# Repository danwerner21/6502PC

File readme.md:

# 6809PC
The 6502PC is a 6502 ATX format board with 512K RAM, 4K ROM, with a flexible programmable MMU, battery backed up RTC, 6551 UART, and 6 ISAish slots.  This computer will run a version of DOS/65 by Richard A. Leary.  

See this repo (https://github.com/danwerner21/6x0x-DOS65) for ROM image and operating system.

## BUGS
On the V1.0 board /VMA is not asserted long enough and needs to be just tied to ground.

Patches:
 Lift Pin 1 of u5 74ls02.  Tie the socket of U5 pin 1 to ground.
 U47 SCRATCH CONNECTION TO PIN 3 ON BOTTOM OF PCB.  TIE U47 PIN 3 TO +5V (DO NOT USE PIN 18 OF U47)

Contrary to what is on the Schematic, the battery connector will not support a supercap, a battery is required.

This is corrected on the V1.1 board.

### Jumper Settings
        J1 - IRQ ASSIGNMENT FOR SLOT J2
        J2 - IRQ ASSIGNMENT FOR SLOT J4
        J5 - IRQ ASSIGNMENT FOR SLOT J6
        J7 - IRQ ASSIGNMENT FOR SLOT J8
        J9 - IRQ ASSIGNMENT FOR SLOT J10        
        J13 - IRQ ASSIGNMENT FOR SLOT J14
        
        K1 - ROM BANK SELECT 1&2-ROM IMAGE AT $6000-$6FFF  3&4-ROM IMAGE AT $7000-$7FFF
        P12- POWER SWITCH (MOMENTARY, ATX CASE SWITCH)
        JP1- RESET SWITCH (MOMENTARY, ATX CASE SWITCH)
        P16- BATTERY CONNECTION, P1=+ P2-4=-  (NON RECHARGEABLE)
        JP3- CTS FORCE HIGH
        P18- CONSOLE SERIAL CONNECTOR
        J11- TTL CONSOLE SERIAL CONNECTOR
        J12- ENABLE POWER TO TTL CONSOLE SERIAL CONNECTOR

### Building the system

### Default Memory Map
            $0000-$E000 - RAM
            $E000-$EFFF - Memory Mapped IO
            $F000-$FFFF - ROM
#### IO MEMORY MAP
            $E000-$EF7F - ISA IO SPACE
            $EF80-$EF8F - ACIA
            $EF90-$EF9F - RTC
            $EFA0-$EFAF - OPEN
            $EFB0-$EFBF - OPEN
            $EFC0-$EFCF - OPEN
            $EFD0-$EFDF - MMU TASK MAP
            $EFE0-$EFEF - MMU REGISTERS
            $EFF0-$EFFF - OPEN

### Bill Of Materials
Reference|Value|Qty|Field1|Description
---------|-----|---|------|-----------
C1-C4,C17|22 uF|5||Polarized capacitor
C5-C16,C18-C27,C29-C33,C36-C54,C56,C58,C62|0.1 uF|49||Unpolarized capacitor
C28|1uF|1||Polarized capacitor
C35|10uF|1||Polarized capacitor
C57|0.01 uF|1||Unpolarized capacitor
C59,C60|15pf|2||Unpolarized capacitor
C61,C63-C66|1.0 uF|5||Polarized capacitor
D1,D2|1N4148|2||Diode
D3,D4|D|2||Diode
J1,J2,J5,J7,J9,J13|IRQ Selection|6||Generic connector, double row, 02x06, odd/even pin numbering scheme (row 1 odd numbers, row 2 even numbers), script generated (kicad-library-utils/schlib/autogen/connector/)
J3,J4,J6,J8,J10,J14|Bus_ISA_8bit|6||8-bit ISA-PC bus connector
J11|TTL SERIAL CONSOLE|1||Generic connector, single row, 01x06, script generated (kicad-library-utils/schlib/autogen/connector/)
J12|TTL CONSOLE PWR|1||Generic connector, single row, 01x02, script generated (kicad-library-utils/schlib/autogen/connector/)
JP1,JP3|JUMPER|2||Generic connector, single row, 01x02, script generated (kicad-library-utils/schlib/autogen/connector/),Jumper, 2-pole, open
K1|ROM SELECT|1||Generic connector, single row, 01x03, script generated (kicad-library-utils/schlib/autogen/connector/)
P1|SHADOW ADDR|1||Generic connector, double row, 02x04, odd/even pin numbering scheme (row 1 odd numbers, row 2 even numbers), script generated (kicad-library-utils/schlib/autogen/connector/)
P11|CONN_10X2|1||Generic connector, double row, 02x10, odd/even pin numbering scheme (row 1 odd numbers, row 2 even numbers), script generated (kicad-library-utils/schlib/autogen/connector/)
P12|POWER_SW|1||Generic connector, single row, 01x02, script generated (kicad-library-utils/schlib/autogen/connector/)
P13|14.31818 MHz CLK|1||
P14|16.000Mhz|1||
P15|CPU CLOCK SPEED|1||Generic connector, double row, 02x04, odd/even pin numbering scheme (row 1 odd numbers, row 2 even numbers), script generated (kicad-library-utils/schlib/autogen/connector/)
P16|CONN_4|1||Generic connector, single row, 01x04, script generated (kicad-library-utils/schlib/autogen/connector/)
P17|1.8432 MHz CLK|1||
P18|SERIAL|1||Generic connector, double row, 02x05, odd/even pin numbering scheme (row 1 odd numbers, row 2 even numbers), script generated (kicad-library-utils/schlib/autogen/connector/)
R1,R3|10k|2||Resistor
R2|470|1||Resistor
R4,R7,R26|4.7K|3||Resistor
R5,R6,R8|1000|3||Resistor
RR1|2200|1||9 resistor network, star topology, bussed resistors, small symbol
RR2|22K|1||9 resistor network, star topology, bussed resistors, small symbol
SW1|POWER|1||Push button switch, generic, two pins
SW2|RESET|1||Push button switch, generic, two pins
U1|74LS04|1||Hex Inverter
U2,U34,U36,U39,U45,U46|74LS244|6||Octal Buffer and Line Driver With 3-State Output, active-low enables, non-inverting outputs
U3|74LS682|1||
U4|74LS86|1||Quad 2-input XOR
U5|74LS02|1||quad 2-input NOR gate
U6,U21|74LS00|2||quad 2-input NAND gate
U7,U10,U16|74LS32|3||Quad 2-input OR
U8|SRAM_512K|1||512K x 8 Low Power CMOS RAM, DIP-32
U9,U15|74LS08|2||Quad And2
U11|27C256|1||OTP EPROM 256 KiBit
U12,U22|74LS74|2||Dual D Flip-flop, Set & Reset
U13|6502|1||8-bit NMOS Microprocessor, 64K, DIP-40
U17|74LS14|1||Hex inverter schmitt trigger
U18|74LS06|1||Inverter Open Collect
U19|74HCT14|1||Hex inverter schmitt trigger
U23|74LS688|1||8-bit magnitude comparator
U24,U42|74LS138|2||Decoder 3 to 8 active low outputs
U25-U28,U32,U41|74LS245|6||Octal BUS Transceivers, 3-State outputs
U29|DS1233|1||
U30|74LS163|1||Synchronous 4-bit programmable binary Counter
U31|74LS240|1||Octal Buffer and Line Driver With 3-State Output, active-low enables, inverting outputs
U35|74LS174|1||Hex D-type Flip-Flop, reset
U37|74LS157|1||Quad 2 to 1 line Multiplexer
U38|74LS374|1||8-bit Register, 3-state outputs
U40|SRAM-32K|1||256K (32K x 8) Static RAM, 70ns, DIP-28
U43,U44|74LS257|2||Quad 2 to 1 Multiplexer
U47|M6242|1||M6242
U48|G65SC51P|1||CMOS Asynchronous Communication Interface Adapter (ACIA), Serial UART, DIP-28
U49|MAX232|1||Dual RS232 driver/receiver, 5V supply, 120kb/s, 0C-70C
X1|RTC_OSC|1|32.768 KHz|Two pin crystal

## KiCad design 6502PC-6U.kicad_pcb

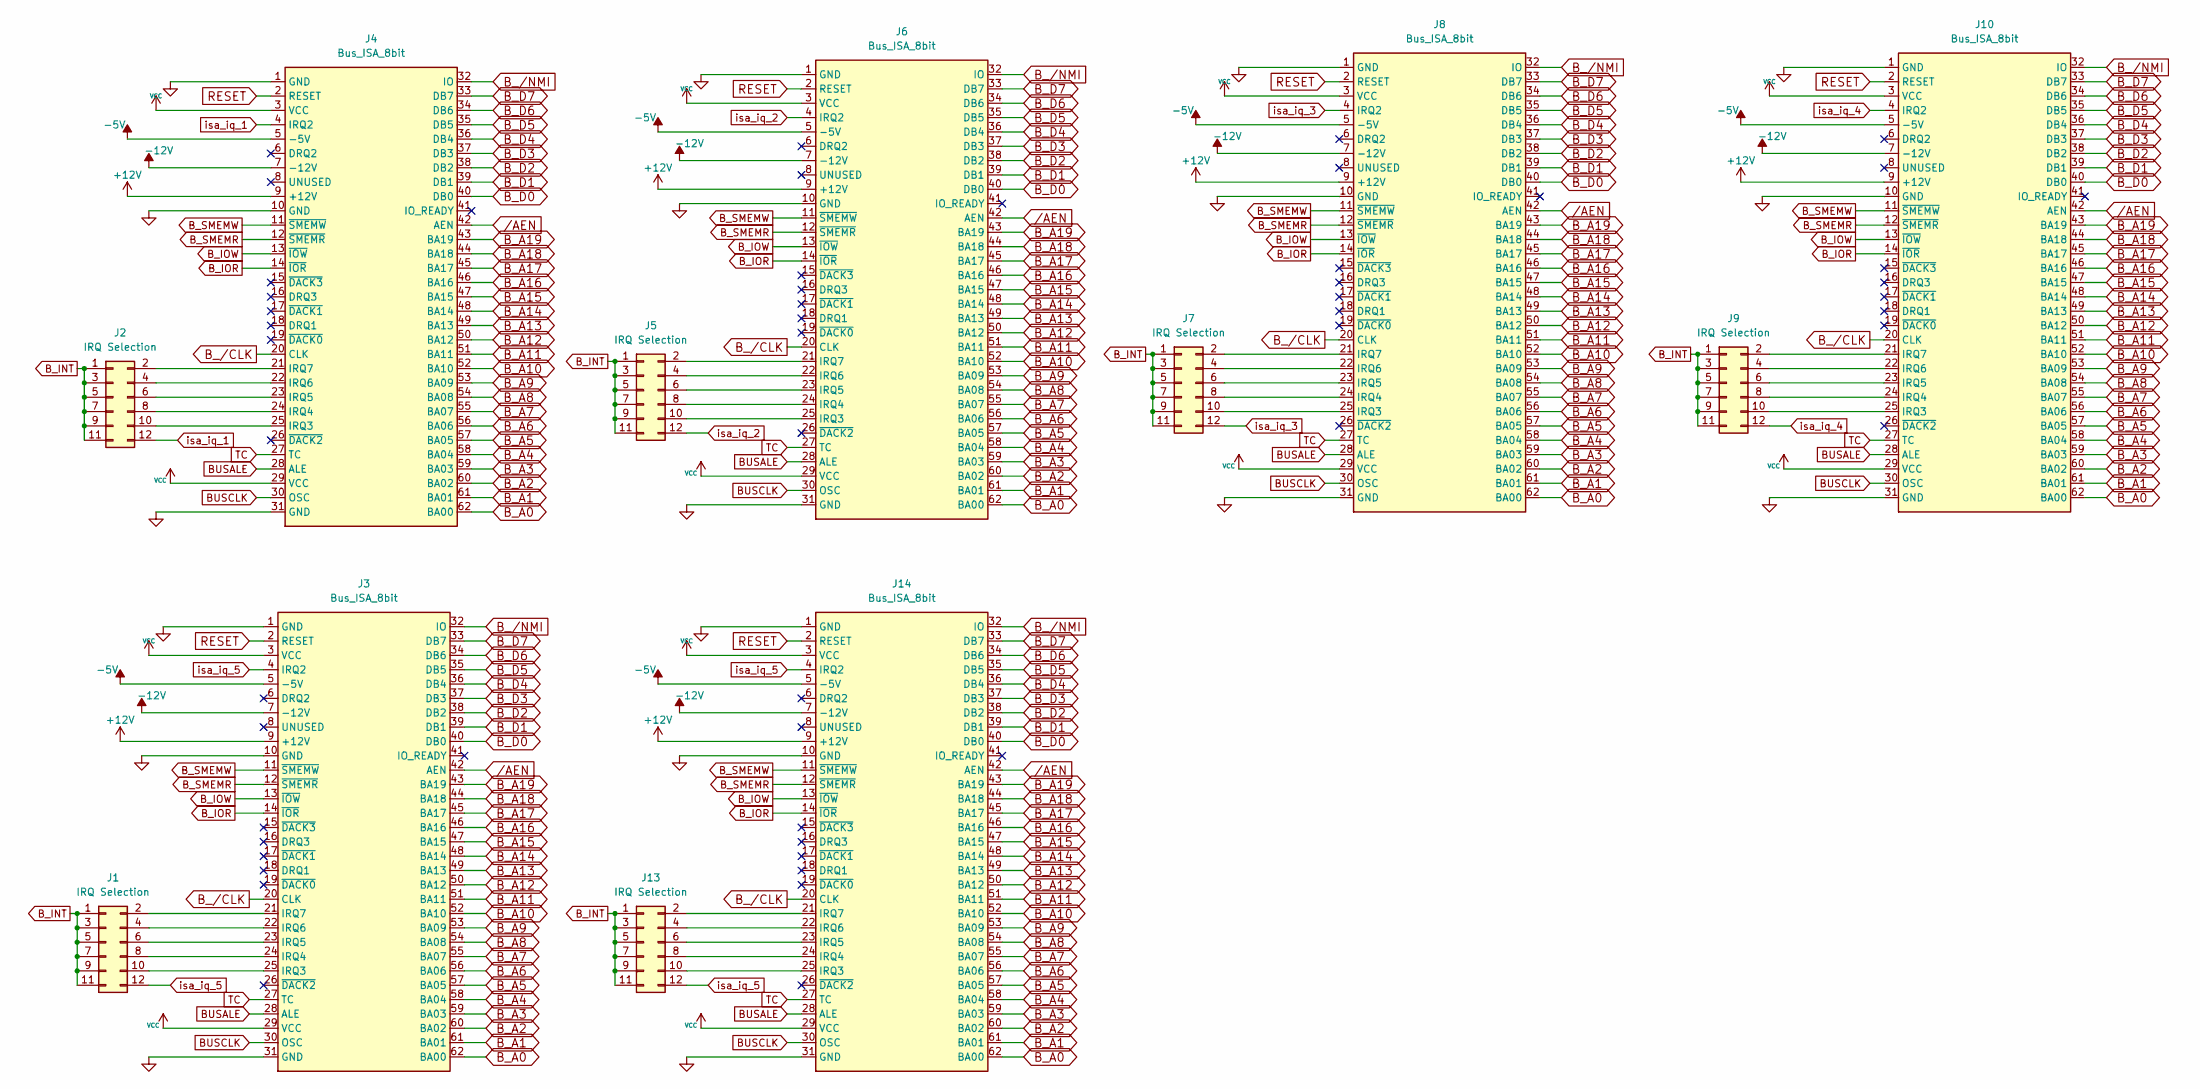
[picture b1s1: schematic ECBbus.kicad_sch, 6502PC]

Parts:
J1, J2, J5, J7, J9, J13: IRQ Selection; STD_DDW_PINHEAD_V_2x06
J3, J4, J6, J8, J10, J14: Bus_ISA_8bit; BUSPC_HOST

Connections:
+5V: J3.3 (VCC), J3.29 (VCC), J4.3 (VCC), J4.29 (VCC), J6.3 (VCC), J6.29 (VCC), J8.3 (VCC), J8.29 (VCC), J10.3 (VCC), J10.29 (VCC), J14.3 (VCC), J14.29 (VCC); also elsewhere on the board
+12V: J3.9 (+12V), J4.9 (+12V), J6.9 (+12V), J8.9 (+12V), J10.9 (+12V), J14.9 (+12V); also elsewhere on the board
-5V: J3.5 (-5V), J4.5 (-5V), J6.5 (-5V), J8.5 (-5V), J10.5 (-5V), J14.5 (-5V); also elsewhere on the board
-12V: J3.7 (-12V), J4.7 (-12V), J6.7 (-12V), J8.7 (-12V), J10.7 (-12V), J14.7 (-12V); also elsewhere on the board
BUSALE: J3.28 (ALE), J4.28 (ALE), J6.28 (ALE), J8.28 (ALE), J10.28 (ALE), J14.28 (ALE); also elsewhere on the board
BUSCLK: J3.30 (OSC), J4.30 (OSC), J6.30 (OSC), J8.30 (OSC), J10.30 (OSC), J14.30 (OSC); also elsewhere on the board
B_A0: J3.62 (BA00), J4.62 (BA00), J6.62 (BA00), J8.62 (BA00), J10.62 (BA00), J14.62 (BA00); also elsewhere on the board
B_A1: J3.61 (BA01), J4.61 (BA01), J6.61 (BA01), J8.61 (BA01), J10.61 (BA01), J14.61 (BA01); also elsewhere on the board
B_A2: J3.60 (BA02), J4.60 (BA02), J6.60 (BA02), J8.60 (BA02), J10.60 (BA02), J14.60 (BA02); also elsewhere on the board
B_A3: J3.59 (BA03), J4.59 (BA03), J6.59 (BA03), J8.59 (BA03), J10.59 (BA03), J14.59 (BA03); also elsewhere on the board
B_A4: J3.58 (BA04), J4.58 (BA04), J6.58 (BA04), J8.58 (BA04), J10.58 (BA04), J14.58 (BA04); also elsewhere on the board
B_A5: J3.57 (BA05), J4.57 (BA05), J6.57 (BA05), J8.57 (BA05), J10.57 (BA05), J14.57 (BA05); also elsewhere on the board
B_A6: J3.56 (BA06), J4.56 (BA06), J6.56 (BA06), J8.56 (BA06), J10.56 (BA06), J14.56 (BA06); also elsewhere on the board
B_A7: J3.55 (BA07), J4.55 (BA07), J6.55 (BA07), J8.55 (BA07), J10.55 (BA07), J14.55 (BA07); also elsewhere on the board
B_A8: J3.54 (BA08), J4.54 (BA08), J6.54 (BA08), J8.54 (BA08), J10.54 (BA08), J14.54 (BA08); also elsewhere on the board
B_A9: J3.53 (BA09), J4.53 (BA09), J6.53 (BA09), J8.53 (BA09), J10.53 (BA09), J14.53 (BA09); also elsewhere on the board
B_A10: J3.52 (BA10), J4.52 (BA10), J6.52 (BA10), J8.52 (BA10), J10.52 (BA10), J14.52 (BA10); also elsewhere on the board
B_A11: J3.51 (BA11), J4.51 (BA11), J6.51 (BA11), J8.51 (BA11), J10.51 (BA11), J14.51 (BA11); also elsewhere on the board
B_A12: J3.50 (BA12), J4.50 (BA12), J6.50 (BA12), J8.50 (BA12), J10.50 (BA12), J14.50 (BA12); also elsewhere on the board
B_A13: J3.49 (BA13), J4.49 (BA13), J6.49 (BA13), J8.49 (BA13), J10.49 (BA13), J14.49 (BA13); also elsewhere on the board
B_A14: J3.48 (BA14), J4.48 (BA14), J6.48 (BA14), J8.48 (BA14), J10.48 (BA14), J14.48 (BA14); also elsewhere on the board
B_A15: J3.47 (BA15), J4.47 (BA15), J6.47 (BA15), J8.47 (BA15), J10.47 (BA15), J14.47 (BA15); also elsewhere on the board
B_A16: J3.46 (BA16), J4.46 (BA16), J6.46 (BA16), J8.46 (BA16), J10.46 (BA16), J14.46 (BA16); also elsewhere on the board
B_A17: J3.45 (BA17), J4.45 (BA17), J6.45 (BA17), J8.45 (BA17), J10.45 (BA17), J14.45 (BA17); also elsewhere on the board
B_A18: J3.44 (BA18), J4.44 (BA18), J6.44 (BA18), J8.44 (BA18), J10.44 (BA18), J14.44 (BA18); also elsewhere on the board
B_A19: J3.43 (BA19), J4.43 (BA19), J6.43 (BA19), J8.43 (BA19), J10.43 (BA19), J14.43 (BA19); also elsewhere on the board
B_D0: J3.40 (DB0), J4.40 (DB0), J6.40 (DB0), J8.40 (DB0), J10.40 (DB0), J14.40 (DB0); also elsewhere on the board
B_D1: J3.39 (DB1), J4.39 (DB1), J6.39 (DB1), J8.39 (DB1), J10.39 (DB1), J14.39 (DB1); also elsewhere on the board
B_D2: J3.38 (DB2), J4.38 (DB2), J6.38 (DB2), J8.38 (DB2), J10.38 (DB2), J14.38 (DB2); also elsewhere on the board
B_D3: J3.37 (DB3), J4.37 (DB3), J6.37 (DB3), J8.37 (DB3), J10.37 (DB3), J14.37 (DB3); also elsewhere on the board
B_D4: J3.36 (DB4), J4.36 (DB4), J6.36 (DB4), J8.36 (DB4), J10.36 (DB4), J14.36 (DB4); also elsewhere on the board
B_D5: J3.35 (DB5), J4.35 (DB5), J6.35 (DB5), J8.35 (DB5), J10.35 (DB5), J14.35 (DB5); also elsewhere on the board
B_D6: J3.34 (DB6), J4.34 (DB6), J6.34 (DB6), J8.34 (DB6), J10.34 (DB6), J14.34 (DB6); also elsewhere on the board
B_D7: J3.33 (DB7), J4.33 (DB7), J6.33 (DB7), J8.33 (DB7), J10.33 (DB7), J14.33 (DB7); also elsewhere on the board
B_INT: J1.1, J1.3, J1.5, J1.7, J1.9, J1.11, J2.1, J2.3, J2.5, J2.7, J2.9, J2.11, J5.1, J5.3, J5.5, J5.7, J5.9, J5.11, J7.1, J7.3, J7.5, J7.7, J7.9, J7.11, J9.1, J9.3, J9.5, J9.7, J9.9, J9.11, J13.1, J13.3, J13.5, J13.7, J13.9, J13.11; also elsewhere on the board
B_IOR: J3.14 (~IOR), J4.14 (~IOR), J6.14 (~IOR), J8.14 (~IOR), J10.14 (~IOR), J14.14 (~IOR); also elsewhere on the board
B_IOW: J3.13 (~IOW), J4.13 (~IOW), J6.13 (~IOW), J8.13 (~IOW), J10.13 (~IOW), J14.13 (~IOW); also elsewhere on the board
B_SMEMR: J3.12 (~SMEMR), J4.12 (~SMEMR), J6.12 (~SMEMR), J8.12 (~SMEMR), J10.12 (~SMEMR), J14.12 (~SMEMR); also elsewhere on the board
B_SMEMW: J3.11 (~SMEMW), J4.11 (~SMEMW), J6.11 (~SMEMW), J8.11 (~SMEMW), J10.11 (~SMEMW), J14.11 (~SMEMW); also elsewhere on the board
B_/CLK: J3.20 (CLK), J4.20 (CLK), J6.20 (CLK), J8.20 (CLK), J10.20 (CLK), J14.20 (CLK); also elsewhere on the board
B_/NMI: J3.32 (IO), J4.32 (IO), J6.32 (IO), J8.32 (IO), J10.32 (IO), J14.32 (IO); also elsewhere on the board
GND: J3.1 (GND), J3.10 (GND), J3.31 (GND), J4.1 (GND), J4.10 (GND), J4.31 (GND), J6.1 (GND), J6.10 (GND), J6.31 (GND), J8.1 (GND), J8.10 (GND), J8.31 (GND), J10.1 (GND), J10.10 (GND), J10.31 (GND), J14.1 (GND), J14.10 (GND), J14.31 (GND); also elsewhere on the board
unnamed: J1.2, J3.21 (IRQ7)
unnamed: J1.4, J3.22 (IRQ6)
unnamed: J1.6, J3.23 (IRQ5)
unnamed: J1.8, J3.24 (IRQ4)
unnamed: J1.10, J3.25 (IRQ3)
unnamed: J2.2, J4.21 (IRQ7)
unnamed: J2.4, J4.22 (IRQ6)
unnamed: J2.6, J4.23 (IRQ5)
unnamed: J2.8, J4.24 (IRQ4)
unnamed: J2.10, J4.25 (IRQ3)
unnamed: J5.2, J6.21 (IRQ7)
unnamed: J5.4, J6.22 (IRQ6)
unnamed: J5.6, J6.23 (IRQ5)
unnamed: J5.8, J6.24 (IRQ4)
unnamed: J5.10, J6.25 (IRQ3)
unnamed: J7.2, J8.21 (IRQ7)
unnamed: J7.4, J8.22 (IRQ6)
unnamed: J7.6, J8.23 (IRQ5)
unnamed: J7.8, J8.24 (IRQ4)
unnamed: J7.10, J8.25 (IRQ3)
unnamed: J9.10, J10.25 (IRQ3)
unnamed: J9.8, J10.24 (IRQ4)
unnamed: J9.6, J10.23 (IRQ5)
unnamed: J9.4, J10.22 (IRQ6)
unnamed: J9.2, J10.21 (IRQ7)
unnamed: J13.2, J14.21 (IRQ7)
unnamed: J13.4, J14.22 (IRQ6)
unnamed: J13.6, J14.23 (IRQ5)
unnamed: J13.8, J14.24 (IRQ4)
unnamed: J13.10, J14.25 (IRQ3)
RESET: J3.2 (RESET), J4.2 (RESET), J6.2 (RESET), J8.2 (RESET), J10.2 (RESET), J14.2 (RESET); also elsewhere on the board
TC: J3.27 (TC), J4.27 (TC), J6.27 (TC), J8.27 (TC), J10.27 (TC), J14.27 (TC); also elsewhere on the board
isa_iq_1: J2.12, J4.4 (IRQ2)
isa_iq_2: J5.12, J6.4 (IRQ2)
isa_iq_3: J7.12, J8.4 (IRQ2)
isa_iq_4: J9.12, J10.4 (IRQ2)
isa_iq_5: J1.12, J3.4 (IRQ2), J13.12, J14.4 (IRQ2)
/AEN: J3.42 (AEN), J4.42 (AEN), J6.42 (AEN), J8.42 (AEN), J10.42 (AEN), J14.42 (AEN); also elsewhere on the board

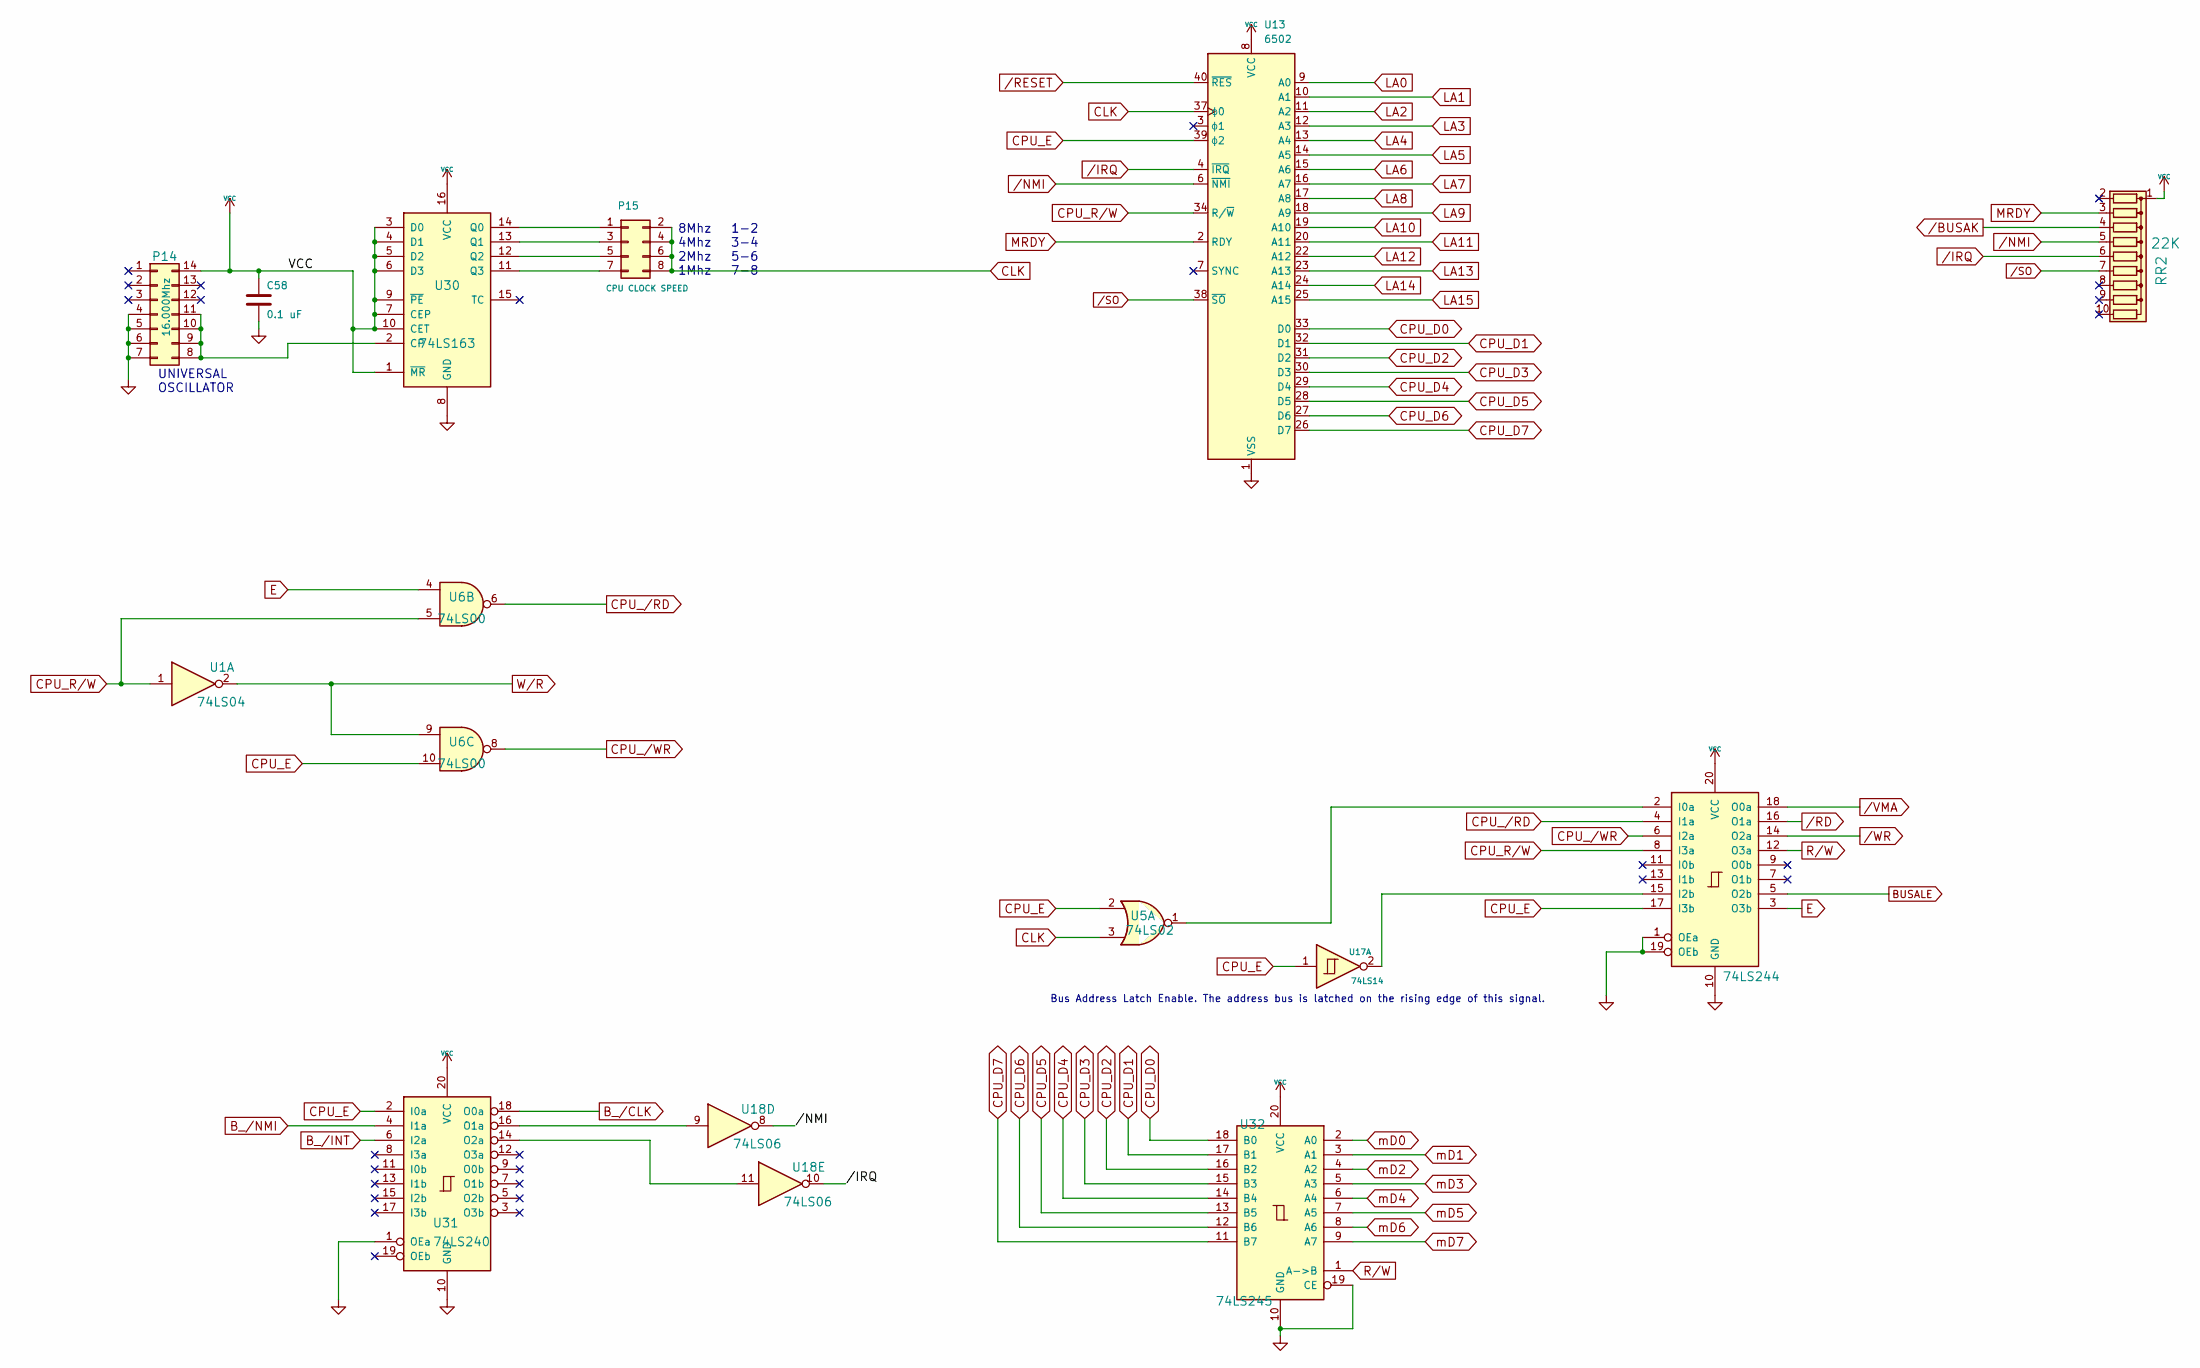
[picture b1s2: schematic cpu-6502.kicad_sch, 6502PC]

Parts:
C58: 0.1 uF; STD_DDW_CAP
P14: 16.000Mhz; STD_DDW_DIP14
P15: CPU CLOCK SPEED; STD_DDW_PINHEAD_V_2x04
RR2: 22K; STD_DDW_SIP10
U1: 74LS04; STD_DDW_DIP14
U5: 74LS02; STD_DDW_DIP14
U6: 74LS00; STD_DDW_DIP14
U13: 6502; DIP-40_W15.24mm
U17: 74LS14; STD_DDW_DIP14
U18: 74LS06; STD_DDW_DIP14
U30: 74LS163; STD_DDW_DIP16
U31: 74LS240; STD_DDW_DIP20
U32: 74LS245; STD_DDW_DIP20
U34: 74LS244; STD_DDW_DIP20

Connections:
+5V: C58.1, P14.14, RR2.1 (common), U13.8 (VCC), U30.1 (~MR), U30.3 (D0), U30.4 (D1), U30.5 (D2), U30.6 (D3), U30.7 (CEP), U30.9 (~PE), U30.10 (CET), U30.16 (VCC), U31.20 (VCC), U32.20 (VCC), U34.20 (VCC); also elsewhere on the board
BUSALE: U34.5 (O2b); also elsewhere on the board
B_/CLK: U31.18 (O0a); also elsewhere on the board
B_/INT: U31.6 (I2a); also elsewhere on the board
B_/NMI: U31.4 (I1a); also elsewhere on the board
CLK: P15.2, P15.4, P15.6, P15.8, U5.3, U13.37 (ϕ0)
CPU_D0: U13.33 (D0), U32.18 (B0)
CPU_D1: U13.32 (D1), U32.17 (B1)
CPU_D2: U13.31 (D2), U32.16 (B2)
CPU_D3: U13.30 (D3), U32.15 (B3)
CPU_D4: U13.29 (D4), U32.14 (B4)
CPU_D5: U13.28 (D5), U32.13 (B5)
CPU_D6: U13.27 (D6), U32.12 (B6)
CPU_D7: U13.26 (D7), U32.11 (B7)
CPU_E: U5.2, U6.10, U13.39 (ϕ2), U17.1, U31.2 (I0a), U34.17 (I3b); also elsewhere on the board
CPU_R/W: U1.1, U6.5, U13.34 (R/~W), U34.8 (I3a); also elsewhere on the board
CPU_/RD: U6.6, U34.4 (I1a); also elsewhere on the board
CPU_/WR: U6.8, U34.6 (I2a); also elsewhere on the board
E: U6.4, U34.3 (O3b); also elsewhere on the board
GND: C58.2, P14.4, P14.5, P14.6, P14.7, U13.1 (VSS), U13.21 (VSS), U30.8 (GND), U31.1 (OEa), U31.10 (GND), U32.10 (GND), U32.19 (CE), U34.1 (OEa), U34.10 (GND), U34.19 (OEb); also elsewhere on the board
LA0: U13.9 (A0); also elsewhere on the board
LA1: U13.10 (A1); also elsewhere on the board
LA2: U13.11 (A2); also elsewhere on the board
LA3: U13.12 (A3); also elsewhere on the board
LA4: U13.13 (A4); also elsewhere on the board
LA5: U13.14 (A5); also elsewhere on the board
LA6: U13.15 (A6); also elsewhere on the board
LA7: U13.16 (A7); also elsewhere on the board
LA8: U13.17 (A8); also elsewhere on the board
LA9: U13.18 (A9); also elsewhere on the board
LA10: U13.19 (A10); also elsewhere on the board
LA11: U13.20 (A11); also elsewhere on the board
LA12: U13.22 (A12); also elsewhere on the board
LA13: U13.23 (A13); also elsewhere on the board
LA14: U13.24 (A14); also elsewhere on the board
LA15: U13.25 (A15); also elsewhere on the board
MRDY: RR2.3 (R2), U13.2 (RDY)
unnamed: P15.1, U30.14 (Q0)
unnamed: P15.3, U30.13 (Q1)
unnamed: P15.5, U30.12 (Q2)
unnamed: P15.7, U30.11 (Q3)
unnamed: P14.8, P14.9, P14.10, P14.11, U30.2 (CP)
unnamed: U18.9, U31.16 (O1a)
unnamed: U18.11, U31.14 (O2a)
unnamed: U5.1, U34.2 (I0a)
unnamed: U17.2, U34.15 (I2b)
R/W: U32.1 (A->B), U34.12 (O3a); also elsewhere on the board
W/R: U1.2, U6.9
mD0: U32.2 (A0); also elsewhere on the board
mD1: U32.3 (A1); also elsewhere on the board
mD2: U32.4 (A2); also elsewhere on the board
mD3: U32.5 (A3); also elsewhere on the board
mD4: U32.6 (A4); also elsewhere on the board
mD5: U32.7 (A5); also elsewhere on the board
mD6: U32.8 (A6); also elsewhere on the board
mD7: U32.9 (A7); also elsewhere on the board
/BUSAK: RR2.4 (R3); also elsewhere on the board
/IRQ: RR2.6 (R5), U13.4 (~IRQ), U18.10; also elsewhere on the board
/NMI: RR2.5 (R4), U13.6 (~NMI), U18.8
/RD: U34.16 (O1a); also elsewhere on the board
/SO: RR2.7 (R6), U13.38 (~SO)
/VMA: U34.18 (O0a); also elsewhere on the board
/WR: U34.14 (O2a); also elsewhere on the board

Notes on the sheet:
8Mhz 1-2 4Mhz 3-4 2Mhz 5-6 1Mhz 7-8
Bus Address Latch Enable. The address bus is latched on the rising edge of this signal.
UNIVERSAL OSCILLATOR

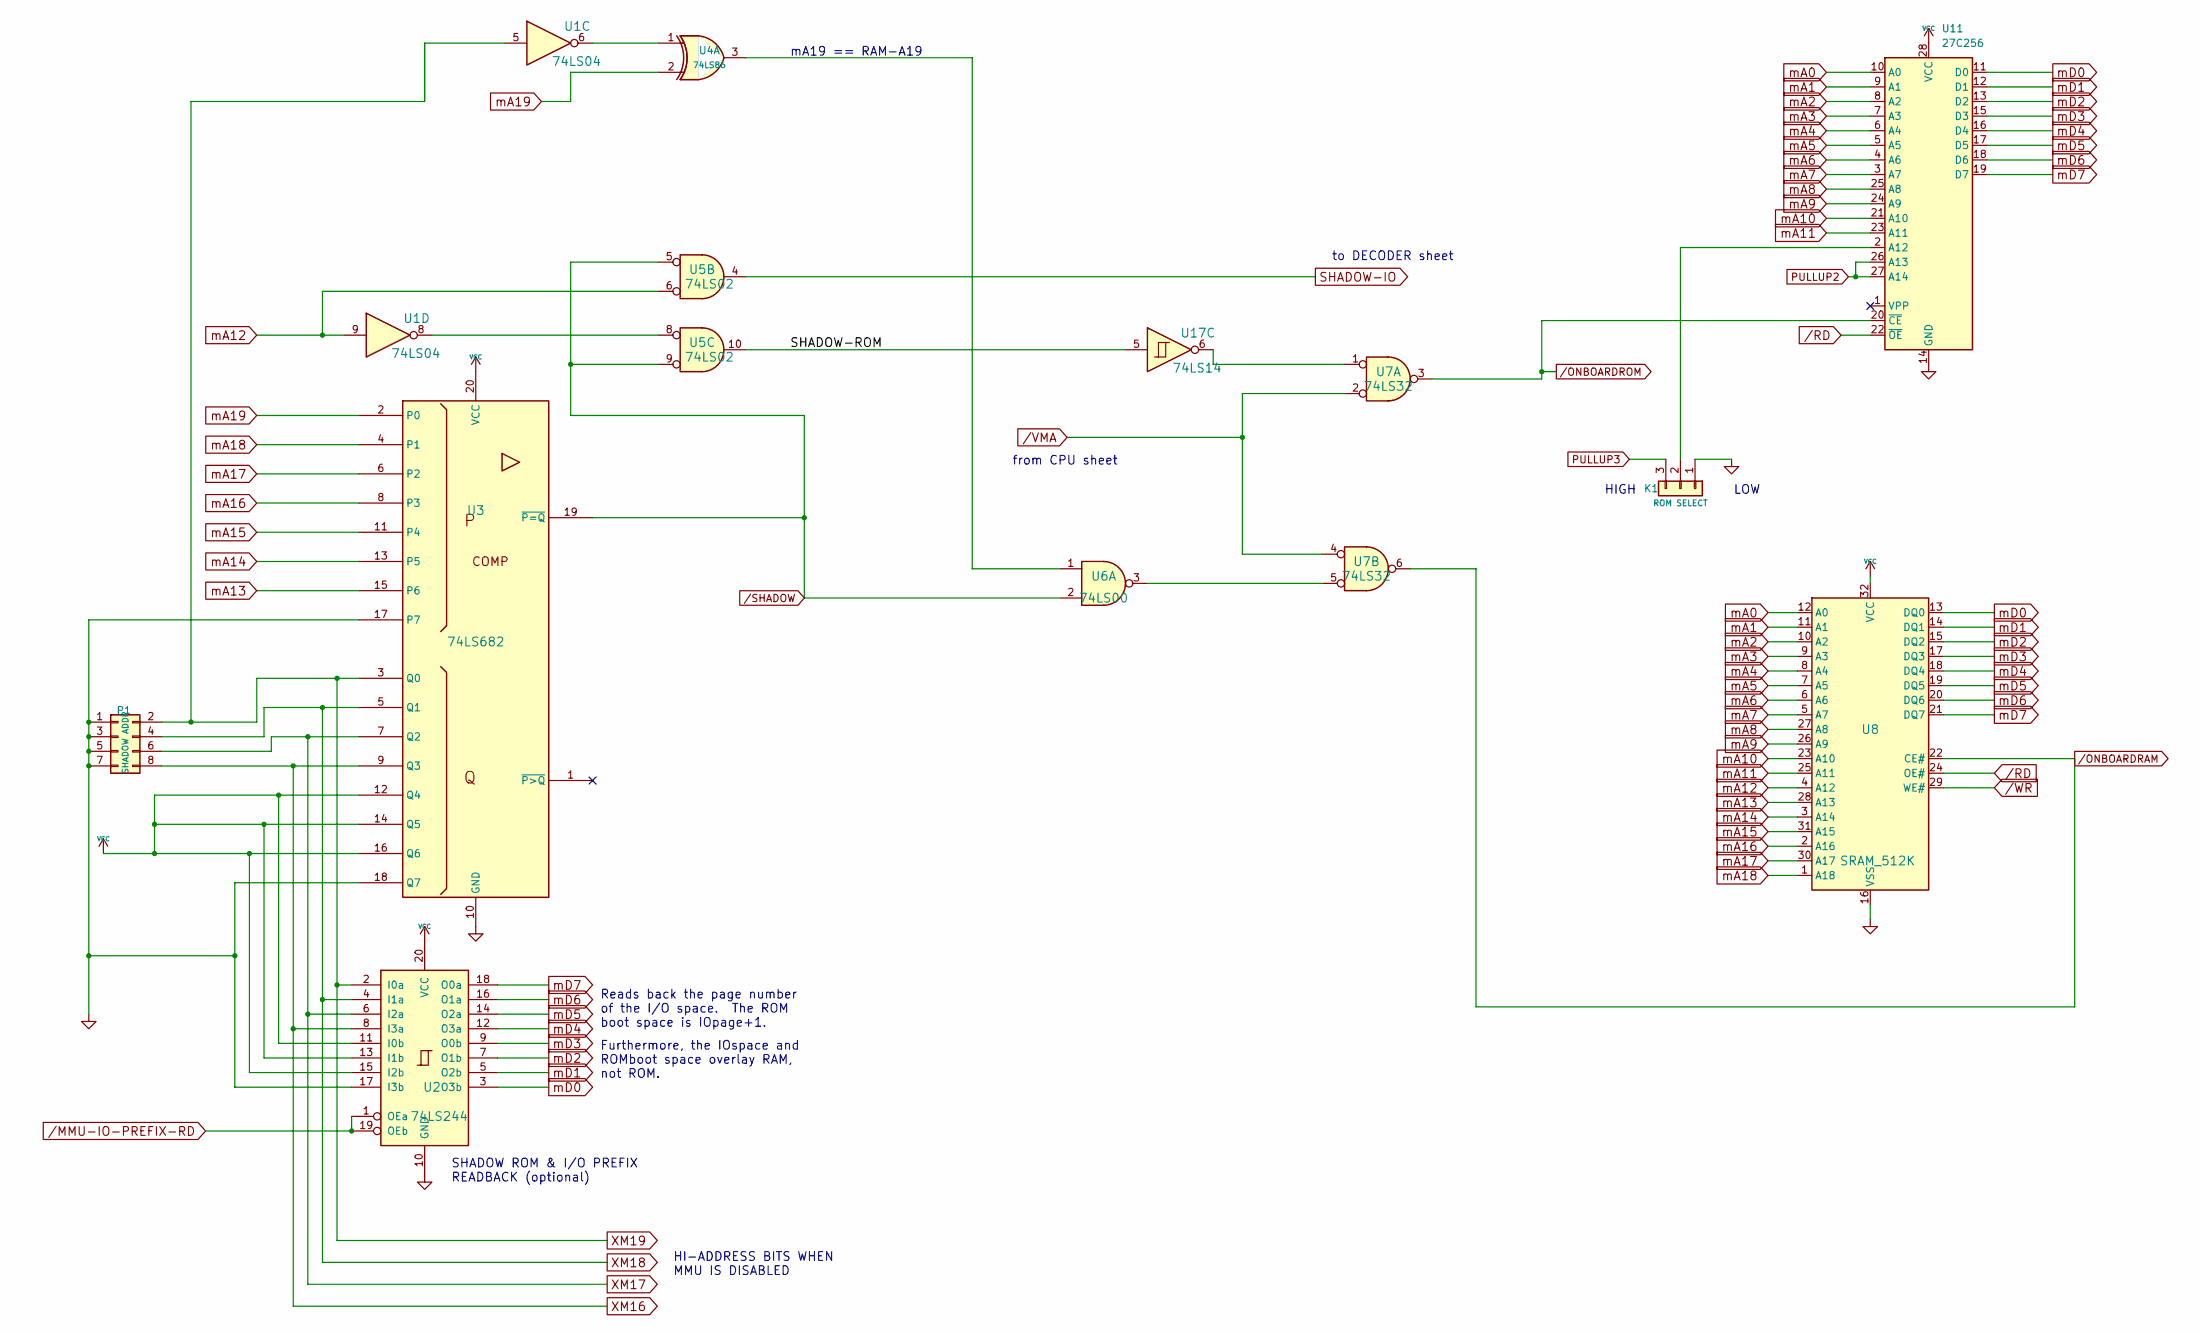
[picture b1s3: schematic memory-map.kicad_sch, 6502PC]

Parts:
K1: ROM SELECT; STD_DDW_PINHEAD_V_1x03
P1: SHADOW ADDR; STD_DDW_PINHEAD_V_2x04
U1: 74LS04; STD_DDW_DIP14
U2: 74LS244; STD_DDW_DIP20
U3: 74LS682; STD_DDW_DIP20
U4: 74LS86; STD_DDW_DIP14
U5: 74LS02; STD_DDW_DIP14
U6: 74LS00; STD_DDW_DIP14
U7: 74LS32; STD_DDW_DIP14
U8: SRAM_512K; STD_DDW_DIP32
U11: 27C256; DIP-28_W15.24mm
U17: 74LS14; STD_DDW_DIP14

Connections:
+5V: U2.11 (I0b), U2.13 (I1b), U2.15 (I2b), U2.20 (VCC), U3.12 (Q4), U3.14 (Q5), U3.16 (Q6), U3.20 (VCC), U8.32 (VCC), U11.28 (VCC); also elsewhere on the board
/Memory Map/SHADOW-ROM: U5.10, U17.5
GND: K1.1, P1.1, P1.3, P1.5, P1.7, U2.10 (GND), U2.17 (I3b), U3.10 (GND), U3.17 (P7), U3.18 (Q7), U8.16 (VSS), U11.14 (GND); also elsewhere on the board
unnamed: K1.2, U11.2 (A12)
unnamed: U1.6, U4.1
unnamed: U1.8, U5.8
unnamed: U4.3, U6.1
unnamed: U6.3, U7.5
unnamed: U7.1, U17.6
PULLUP2: U11.26 (A13), U11.27 (A14); also elsewhere on the board
PULLUP3: K1.3; also elsewhere on the board
SHADOW-IO: U5.4; also elsewhere on the board
XM16: P1.8, U2.8 (I3a), U3.9 (Q3); also elsewhere on the board
XM17: P1.6, U2.6 (I2a), U3.7 (Q2); also elsewhere on the board
XM18: P1.4, U2.4 (I1a), U3.5 (Q1); also elsewhere on the board
XM19: P1.2, U1.5, U2.2 (I0a), U3.3 (Q0); also elsewhere on the board
mA0: U8.12 (A0), U11.10 (A0); also elsewhere on the board
mA1: U8.11 (A1), U11.9 (A1); also elsewhere on the board
mA2: U8.10 (A2), U11.8 (A2); also elsewhere on the board
mA3: U8.9 (A3), U11.7 (A3); also elsewhere on the board
mA4: U8.8 (A4), U11.6 (A4); also elsewhere on the board
mA5: U8.7 (A5), U11.5 (A5); also elsewhere on the board
mA6: U8.6 (A6), U11.4 (A6); also elsewhere on the board
mA7: U8.5 (A7), U11.3 (A7); also elsewhere on the board
mA8: U8.27 (A8), U11.25 (A8); also elsewhere on the board
mA9: U8.26 (A9), U11.24 (A9); also elsewhere on the board
mA10: U8.23 (A10), U11.21 (A10); also elsewhere on the board
mA11: U8.25 (A11), U11.23 (A11); also elsewhere on the board
mA12: U1.9, U5.6, U8.4 (A12); also elsewhere on the board
mA13: U3.15 (P6), U8.28 (A13); also elsewhere on the board
mA14: U3.13 (P5), U8.3 (A14); also elsewhere on the board
mA15: U3.11 (P4), U8.31 (A15); also elsewhere on the board
mA16: U3.8 (P3), U8.2 (A16); also elsewhere on the board
mA17: U3.6 (P2), U8.30 (A17); also elsewhere on the board
mA18: U3.4 (P1), U8.1 (A18); also elsewhere on the board
mA19: U3.2 (P0), U4.2; also elsewhere on the board
mD0: U2.3 (O3b), U8.13 (DQ0), U11.11 (D0); also elsewhere on the board
mD1: U2.5 (O2b), U8.14 (DQ1), U11.12 (D1); also elsewhere on the board
mD2: U2.7 (O1b), U8.15 (DQ2), U11.13 (D2); also elsewhere on the board
mD3: U2.9 (O0b), U8.17 (DQ3), U11.15 (D3); also elsewhere on the board
mD4: U2.12 (O3a), U8.18 (DQ4), U11.16 (D4); also elsewhere on the board
mD5: U2.14 (O2a), U8.19 (DQ5), U11.17 (D5); also elsewhere on the board
mD6: U2.16 (O1a), U8.20 (DQ6), U11.18 (D6); also elsewhere on the board
mD7: U2.18 (O0a), U8.21 (DQ7), U11.19 (D7); also elsewhere on the board
/MMU-IO-PREFIX-RD: U2.1 (OEa), U2.19 (OEb); also elsewhere on the board
/ONBOARDRAM: U7.6, U8.22 (CE#); also elsewhere on the board
/ONBOARDROM: U7.3, U11.20 (~CE); also elsewhere on the board
/RD: U8.24 (OE#), U11.22 (~OE); also elsewhere on the board
/SHADOW: U3.19 (~P=Q), U5.5, U5.9, U6.2
/VMA: U7.2, U7.4; also elsewhere on the board
/WR: U8.29 (WE#); also elsewhere on the board

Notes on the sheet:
mA19 == RAM-A19
SHADOW ROM & I/O PREFIX READBACK (optional)
Reads back the page number of the I/O space. The ROM boot space is IOpage+1.
HIGH
Furthermore, the IOspace and ROMboot space overlay RAM, not ROM.
from CPU sheet
HI-ADDRESS BITS WHEN MMU IS DISABLED
LOW
to DECODER sheet
